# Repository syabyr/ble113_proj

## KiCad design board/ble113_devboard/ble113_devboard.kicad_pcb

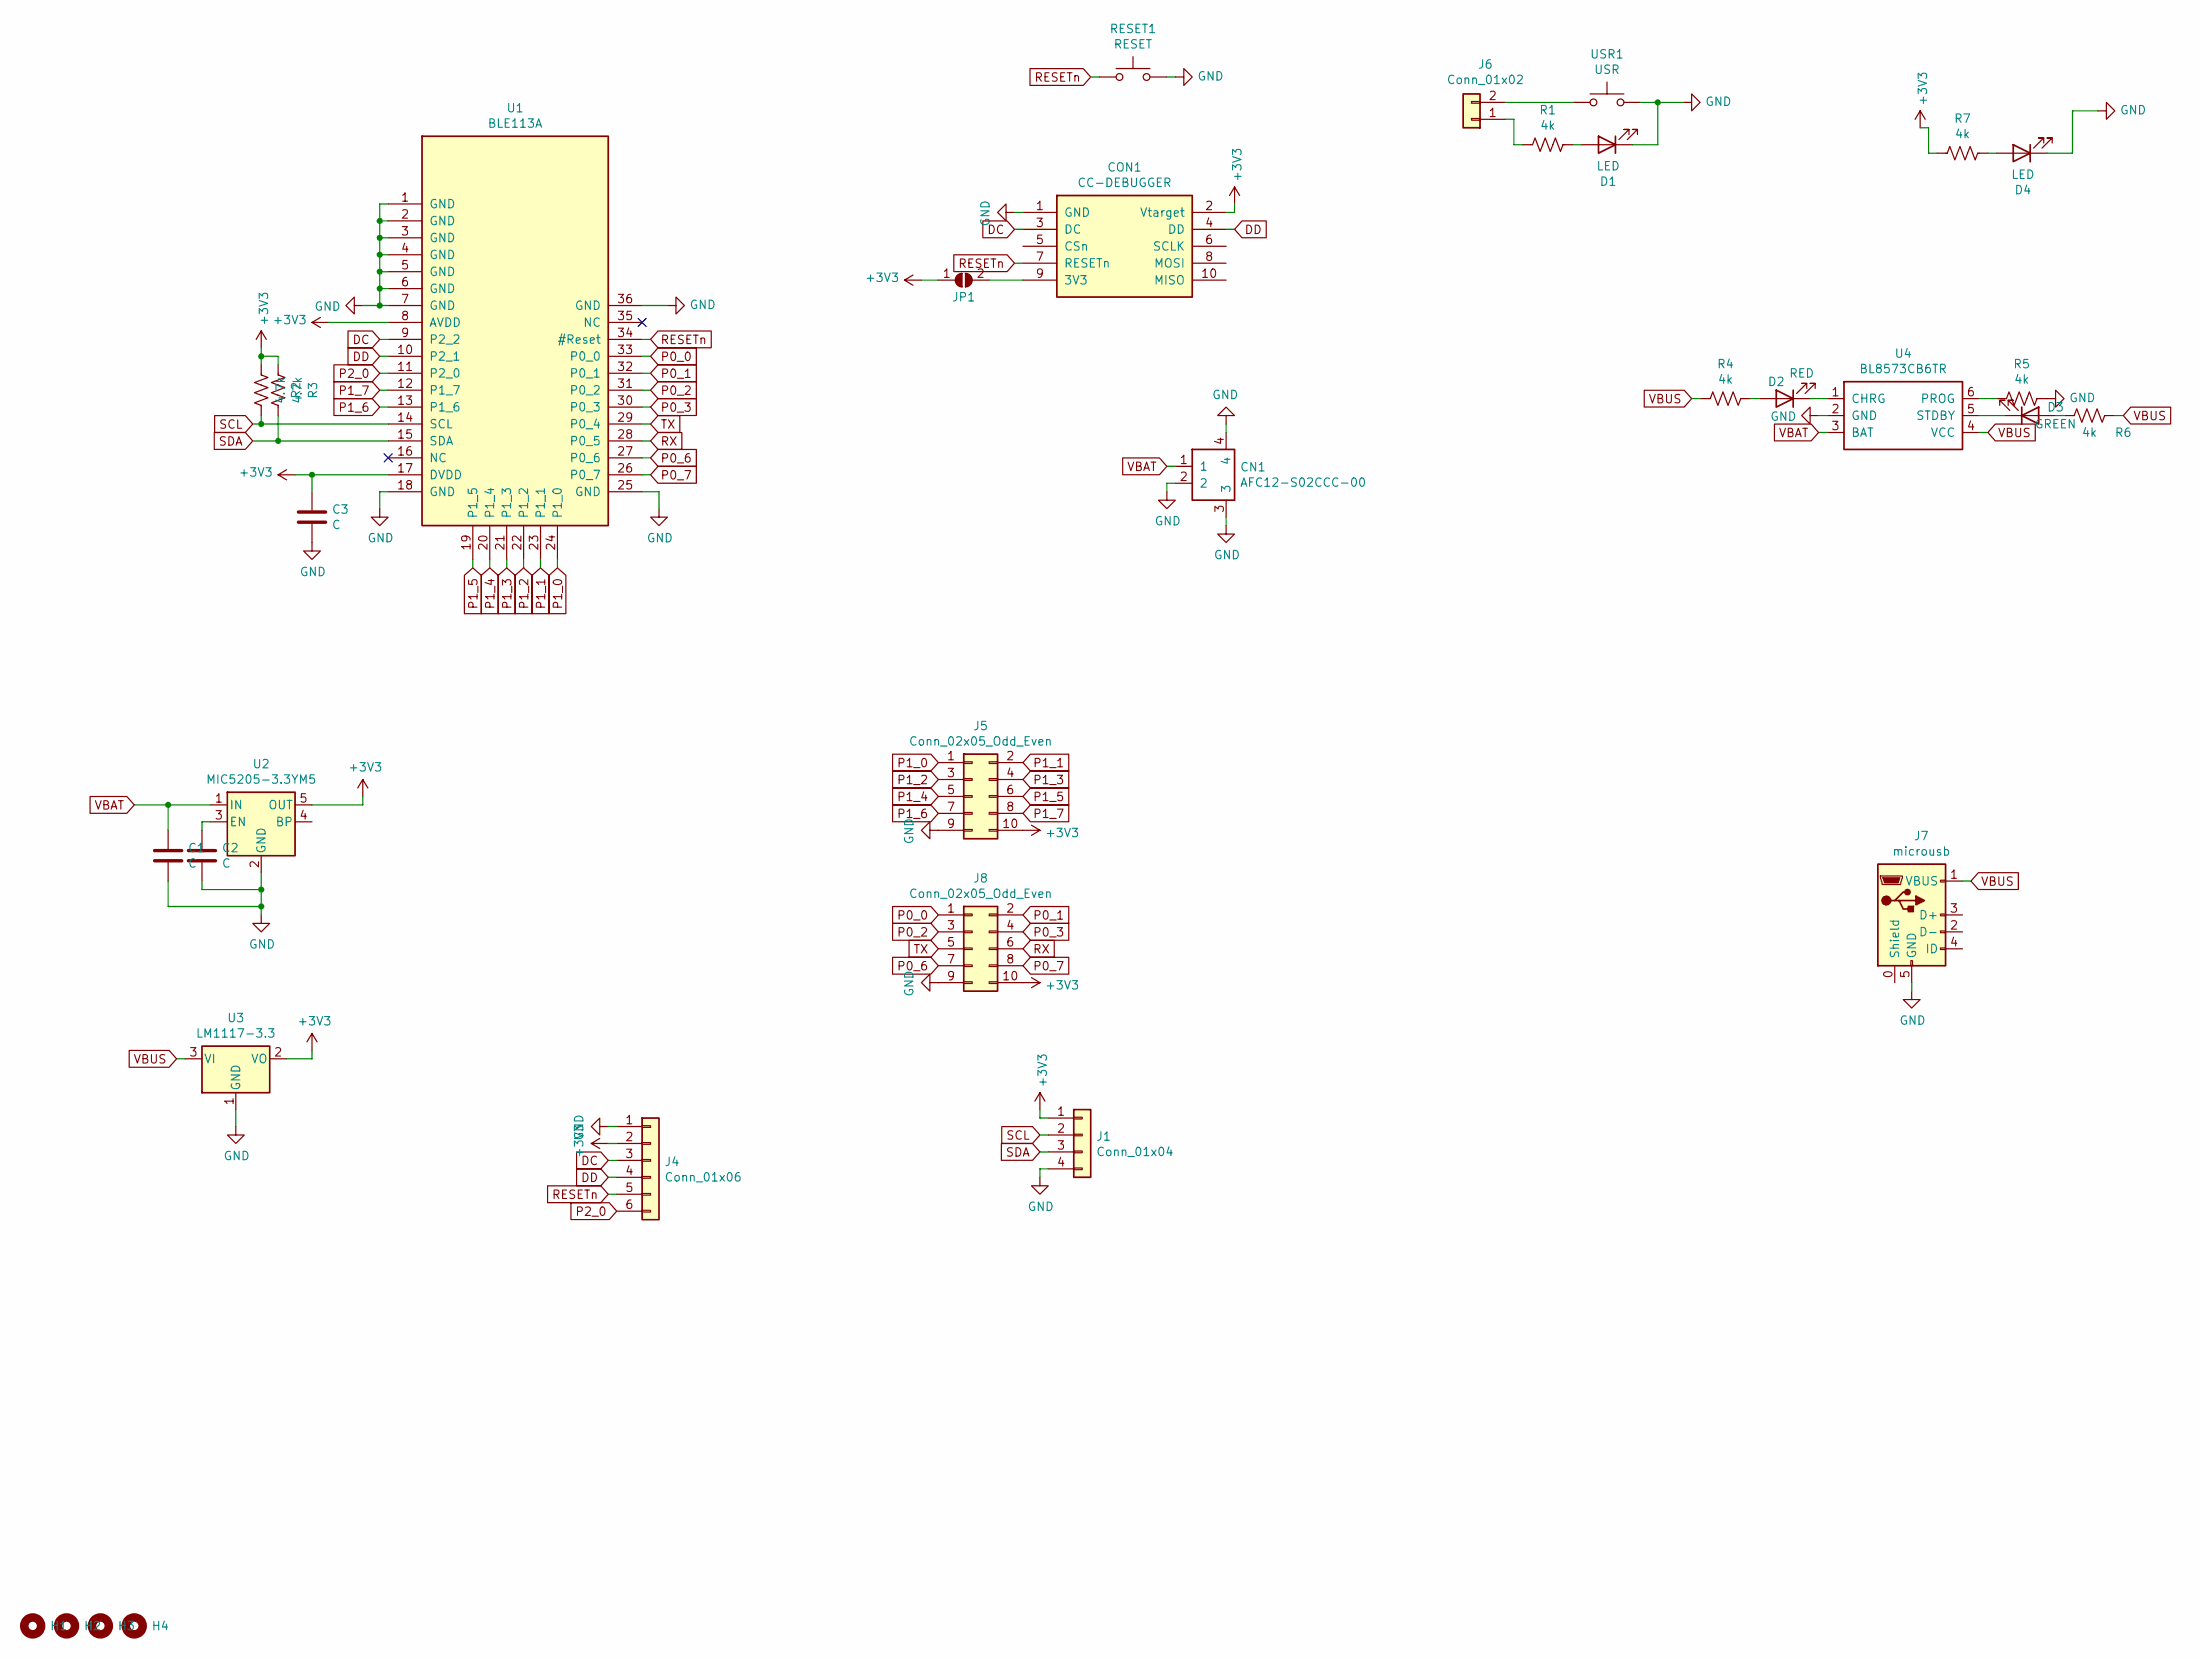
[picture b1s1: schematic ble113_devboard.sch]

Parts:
C1, C3: C; C_0805_2012Metric_Pad1.18x1.45mm_HandSolder
C2: C; C_0402_1005Metric_Pad0.74x0.62mm_HandSolder
CN1: AFC12-S02CCC-00; CONN-SMD_AFC12-S02CCC-00
CON1: CC-DEBUGGER; debugger_2x05_P1.27mm_Vertical
D1, D4: LED; LED_0603_1608Metric_Pad1.05x0.95mm_HandSolder
D2: RED; LED_0603_1608Metric_Pad1.05x0.95mm_HandSolder
D3: GREEN; LED_0603_1608Metric_Pad1.05x0.95mm_HandSolder
H1, H2, H3, H4: MountingHole; MountingHole_3.2mm_M3_ISO7380
J1: Conn_01x04; PinHeader_1x04_P2.54mm_Vertical
J4: Conn_01x06; PinHeader_1x06_P2.54mm_Vertical
J5, J8: Conn_02x05_Odd_Even; PinHeader_2x05_P2.54mm_Vertical
J6: Conn_01x02; PinHeader_1x02_P2.54mm_Vertical
J7: microusb; USB_Micro-B_Wuerth_629105150521_CircularHoles
JP1: SolderJumper_2_Open; SolderJumper-2_P1.3mm_Open_Pad1.0x1.5mm
R1, R4, R5, R6, R7: 4k; R_0402_1005Metric_Pad0.72x0.64mm_HandSolder
R2, R3: 4.7k; R_0402_1005Metric_Pad0.72x0.64mm_HandSolder
RESET1: RESET; turtlekey
U1: BLE113A; BLE113
U2: MIC5205-3.3YM5; SOT-23-5
U3: LM1117-3.3; SOT-223-3_TabPin2
U4: BL8573CB6TR; SOT-23-6_Handsoldering
USR1: USR; turtlekey

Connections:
+3V3: C3.1, CON1.2 (Vtarget), J1.1, J4.2, J5.10, J8.10, JP1.1 (A), R2.2, R3.2, R7.2, U1.8 (AVDD), U1.17 (DVDD), U2.5 (OUT), U3.2 (VO)
DC: CON1.3 (DC), J4.3, U1.9 (P2_2)
DD: CON1.4 (DD), J4.4, U1.10 (P2_1)
GND: C1.2, C2.2, C3.2, CN1.2, CN1.3, CN1.4, CON1.1 (GND), D1.1 (K), D4.1 (K), J1.4, J4.1, J5.9, J7.5 (GND), J8.9, R5.1, RESET1.2, U1.1 (GND), U1.2 (GND), U1.3 (GND), U1.4 (GND), U1.5 (GND), U1.6 (GND), U1.7 (GND), U1.18 (GND), U1.25 (GND), U1.36 (GND), U2.2 (GND), U3.1 (GND), U4.2 (GND), USR1.2
unnamed: C2.1, U2.3 (EN)
unnamed: CON1.9 (3V3), JP1.2 (B)
unnamed: D1.2 (A), R1.1
unnamed: D2.1 (K), U4.1 (CHRG)
unnamed: D2.2 (A), R4.1
unnamed: D3.1 (K), U4.5 (STDBY)
unnamed: D3.2 (A), R6.2
unnamed: D4.2 (A), R7.1
unnamed: J6.1, R1.2
unnamed: J6.2, USR1.1
unnamed: R5.2, U4.6 (PROG)
P0_0: J8.1, U1.33 (P0_0)
P0_1: J8.2, U1.32 (P0_1)
P0_2: J8.3, U1.31 (P0_2)
P0_3: J8.4, U1.30 (P0_3)
P0_6: J8.7, U1.27 (P0_6)
P0_7: J8.8, U1.26 (P0_7)
P1_0: J5.1, U1.24 (P1_0)
P1_1: J5.2, U1.23 (P1_1)
P1_2: J5.3, U1.22 (P1_2)
P1_3: J5.4, U1.21 (P1_3)
P1_4: J5.5, U1.20 (P1_4)
P1_5: J5.6, U1.19 (P1_5)
P1_6: J5.7, U1.13 (P1_6)
P1_7: J5.8, U1.12 (P1_7)
P2_0: J4.6, U1.11 (P2_0)
RESETn: CON1.7 (RESETn), J4.5, RESET1.1, U1.34 (#Reset)
RX: J8.6, U1.28 (P0_5)
SCL: J1.2, R2.1, U1.14 (SCL)
SDA: J1.3, R3.1, U1.15 (SDA)
TX: J8.5, U1.29 (P0_4)
VBAT: C1.1, CN1.1, U2.1 (IN), U4.3 (BAT)
VBUS: J7.1 (VBUS), R4.2, R6.1, U3.3 (VI), U4.4 (VCC)

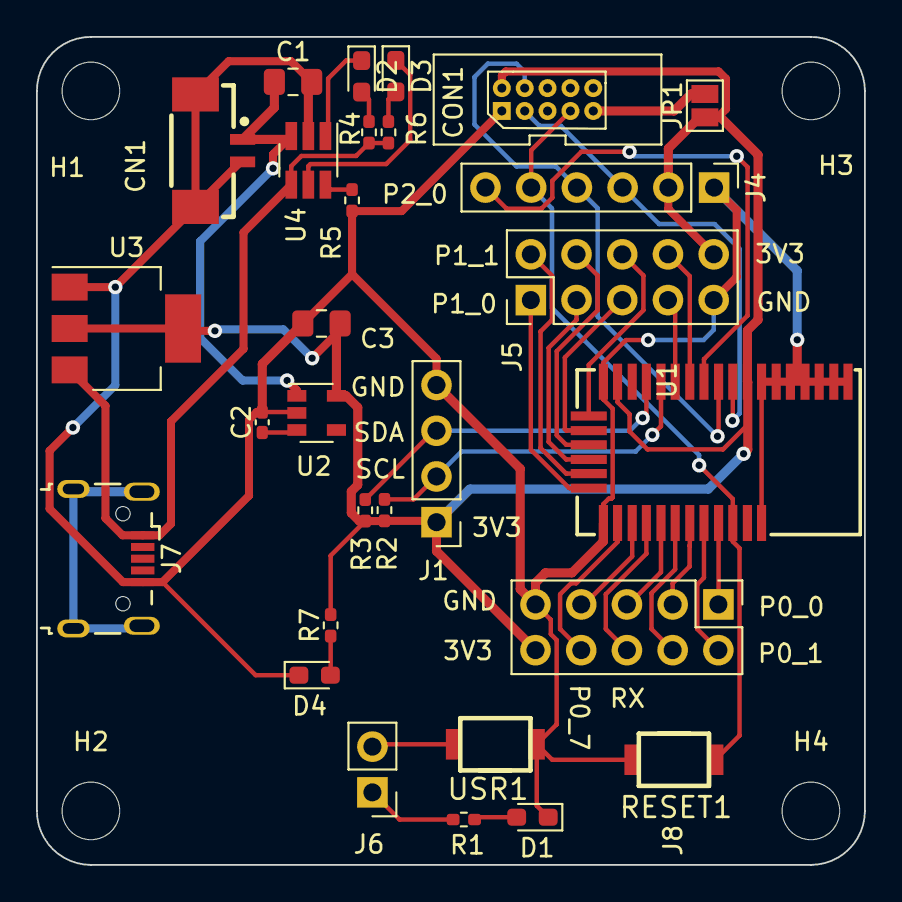
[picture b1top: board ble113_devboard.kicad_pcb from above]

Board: 2 copper layers, 46.0 x 46.0 mm, 33 parts (0 on the bottom side), 37 nets.

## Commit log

2020-10-11 BLE113-A-M256K
2021-07-24 devboard
